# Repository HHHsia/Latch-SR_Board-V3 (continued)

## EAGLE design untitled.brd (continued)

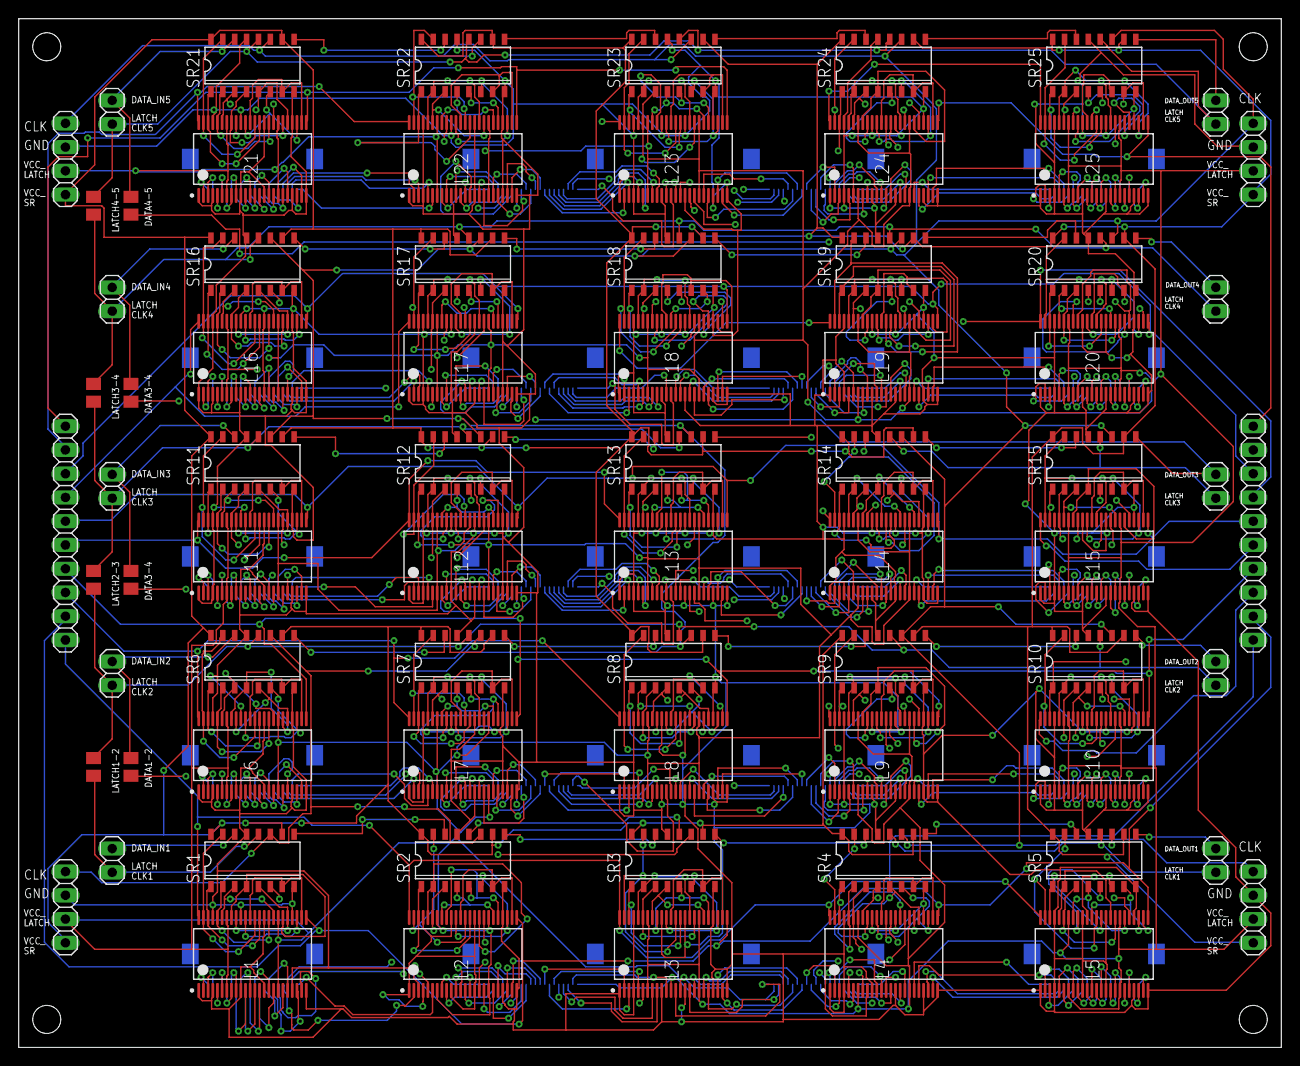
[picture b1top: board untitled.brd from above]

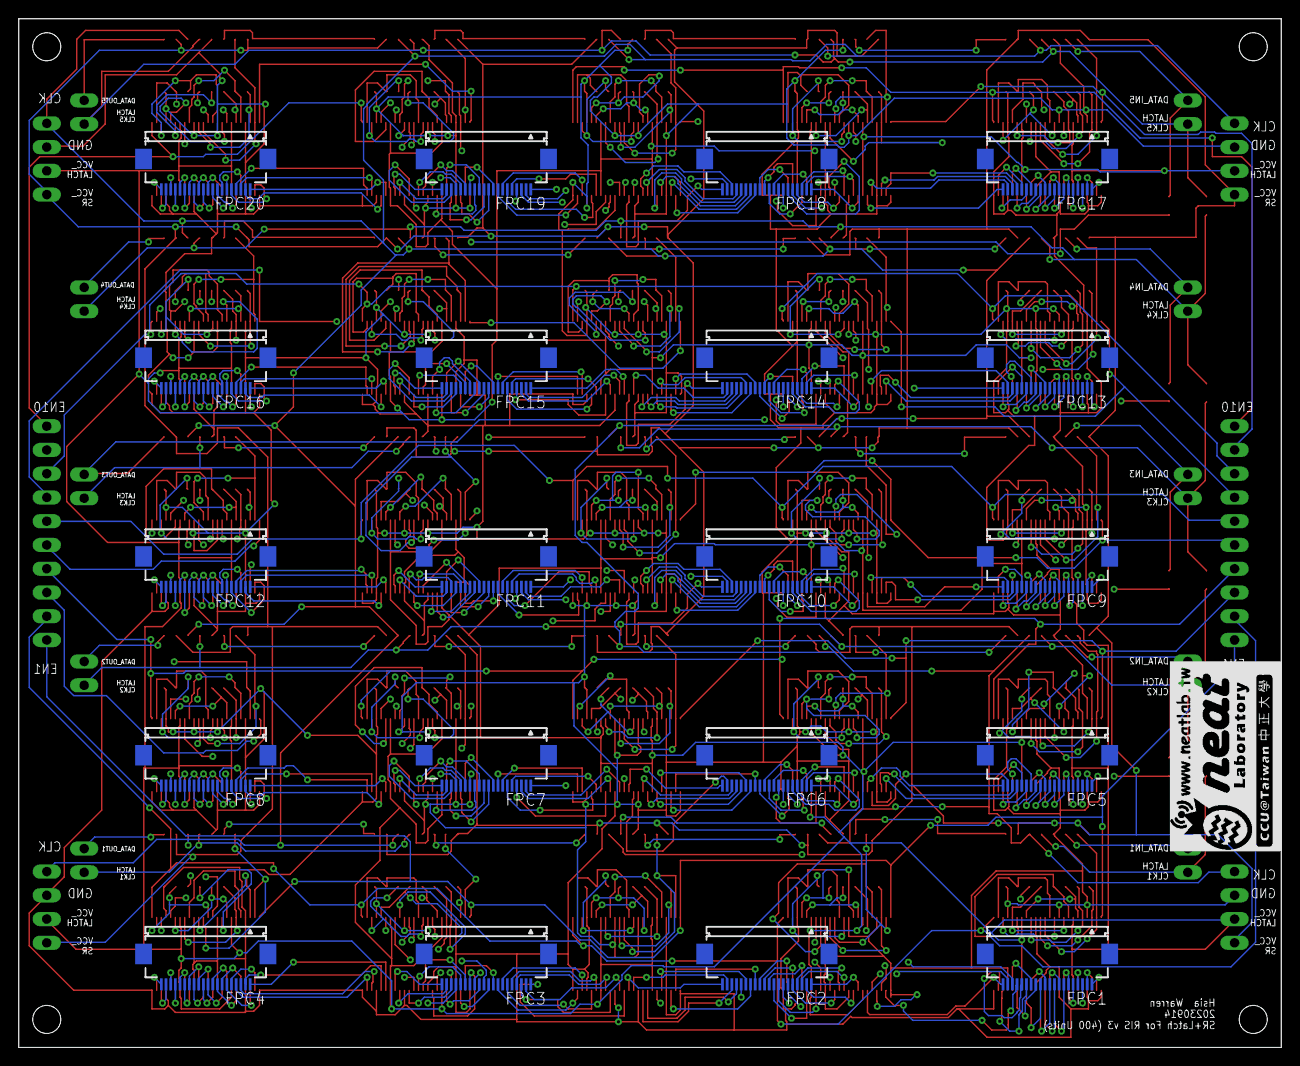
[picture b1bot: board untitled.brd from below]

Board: 4 copper layers, 135.0 x 110.0 mm, 95 parts (21 on the bottom side), 649 nets.

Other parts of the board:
U$1: LOGO_SCALE_2.0

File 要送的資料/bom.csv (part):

"Part";"Value";"Device";"Package";"Description";"3_STATE_OUTPUT";"AVAILABILITY";"BITS";"CIIVA_IDS";"CODE__JEDEC";"DATASHEET_VERSION";"DESCRIPTION";"FOOTPRINT_VARIANT_NAME_0";"FOOTPRINT_VARIANT_NAME_1";"FOOTPRINT_VARIANT_NAME_2";"F__NOM_VOLTAGEMAXMHZ";"ICC__NOM_VOLTAGEMAXMA";"IMPORTED";"IMPORTED_FROM";"IMPORT_TS";"INPUT_TYPE";"LOGIC";"MF";"MP";"MPN";"OC_FARNELL";"OC_NEWARK";"OPERATING_TEMPERATURE_RANGEC";"OUTPUT_DRIVE_IOLIOHMAXMA";"OUTPUT_LOGIC";"OUTPUT_TYPE";"PACKAGE";"POPULARITY";"PREFIX";"PRICE";"RATING";"RELEASE_DATE";"SCHMITT_TRIGGER";"SPICEPREFIX";"STATIC_CURRENT";"TECHNOLOGY_FAMILY";"TPD__NOM_VOLTAGEMAXNS";"VAULT_GUID";"VAULT_REVISION";"VCC_MAX_V";"VCC_MIN_V";"VOLTAGE_NOM_V";
"CONNECTION_BETWEEN_SR5-6";"0R";"R-US_M0805";"M0805";"RESISTOR, American symbol";"";"";"";"";"";"";"";"";"";"";"";"";"";"";"";"";"";"";"";"";"";"";"";"";"";"";"";"45";"";"";"";"";"";"R";"";"";"";"";"";"";"";"";
"CONNECTION_BETWEEN_SR10-11";"0R";"R-US_M0805";"M0805";"RESISTOR, American symbol";"";"";"";"";"";"";"";"";"";"";"";"";"";"";"";"";"";"";"";"";"";"";"";"";"";"";"";"45";"";"";"";"";"";"R";"";"";"";"";"";"";"";"";
"CONNECTION_BETWEEN_SR15-16";"0R";"R-US_M0805";"M0805";"RESISTOR, American symbol";"";"";"";"";"";"";"";"";"";"";"";"";"";"";"";"";"";"";"";"";"";"";"";"";"";"";"";"45";"";"";"";"";"";"R";"";"";"";"";"";"";"";"";
"CONNECTION_BETWEEN_SR20-21";"0R";"R-US_M0805";"M0805";"RESISTOR, American symbol";"";"";"";"";"";"";"";"";"";"";"";"";"";"";"";"";"";"";"";"";"";"";"";"";"";"";"";"45";"";"";"";"";"";"R";"";"";"";"";"";"";"";"";
"EN_JP1";"";"PINHD-1X10";"1X10";"PIN HEADER";"";"";"";"";"";"";"";"";"";"";"";"";"";"";"";"";"";"";"";"";"";"";"";"";"";"";"";"35";"";"";"";"";"";"";"";"";"";"";"";"";"";"";
"EN_JP2";"";"PINHD-1X10";"1X10";"PIN HEADER";"";"";"";"";"";"";"";"";"";"";"";"";"";"";"";"";"";"";"";"";"";"";"";"";"";"";"";"35";"";"";"";"";"";"";"";"";"";"";"";"";"";"";
"FPC1";"FH12-20S-0.5SH";"FH12-20S-0.5SH";"FH12-20S-0.5SH";"0.5mm Pitch Connectors For FPC/FFC";"";"";"";"";"";"";"";"";"";"";"";"";"";"";"";"";"";"";"";"FH12-20S-0.5SH(55)";"1324549";"34M6166";"";"";"";"";"";"0";"";"";"";"";"";"";"";"";"";"";"";"";"";"";
"FPC2";"FH12-20S-0.5SH";"FH12-20S-0.5SH";"FH12-20S-0.5SH";"0.5mm Pitch Connectors For FPC/FFC";"";"";"";"";"";"";"";"";"";"";"";"";"";"";"";"";"";"";"";"FH12-20S-0.5SH(55)";"1324549";"34M6166";"";"";"";"";"";"0";"";"";"";"";"";"";"";"";"";"";"";"";"";"";
"FPC3";"FH12-20S-0.5SH";"FH12-20S-0.5SH";"FH12-20S-0.5SH";"0.5mm Pitch Connectors For FPC/FFC";"";"";"";"";"";"";"";"";"";"";"";"";"";"";"";"";"";"";"";"FH12-20S-0.5SH(55)";"1324549";"34M6166";"";"";"";"";"";"0";"";"";"";"";"";"";"";"";"";"";"";"";"";"";
"FPC4";"FH12-20S-0.5SH";"FH12-20S-0.5SH";"FH12-20S-0.5SH";"0.5mm Pitch Connectors For FPC/FFC";"";"";"";"";"";"";"";"";"";"";"";"";"";"";"";"";"";"";"";"FH12-20S-0.5SH(55)";"1324549";"34M6166";"";"";"";"";"";"0";"";"";"";"";"";"";"";"";"";"";"";"";"";"";
"FPC5";"FH12-20S-0.5SH";"FH12-20S-0.5SH";"FH12-20S-0.5SH";"0.5mm Pitch Connectors For FPC/FFC";"";"";"";"";"";"";"";"";"";"";"";"";"";"";"";"";"";"";"";"FH12-20S-0.5SH(55)";"1324549";"34M6166";"";"";"";"";"";"0";"";"";"";"";"";"";"";"";"";"";"";"";"";"";
"FPC6";"FH12-20S-0.5SH";"FH12-20S-0.5SH";"FH12-20S-0.5SH";"0.5mm Pitch Connectors For FPC/FFC";"";"";"";"";"";"";"";"";"";"";"";"";"";"";"";"";"";"";"";"FH12-20S-0.5SH(55)";"1324549";"34M6166";"";"";"";"";"";"0";"";"";"";"";"";"";"";"";"";"";"";"";"";"";
"FPC7";"FH12-20S-0.5SH";"FH12-20S-0.5SH";"FH12-20S-0.5SH";"0.5mm Pitch Connectors For FPC/FFC";"";"";"";"";"";"";"";"";"";"";"";"";"";"";"";"";"";"";"";"FH12-20S-0.5SH(55)";"1324549";"34M6166";"";"";"";"";"";"0";"";"";"";"";"";"";"";"";"";"";"";"";"";"";
"FPC8";"FH12-20S-0.5SH";"FH12-20S-0.5SH";"FH12-20S-0.5SH";"0.5mm Pitch Connectors For FPC/FFC";"";"";"";"";"";"";"";"";"";"";"";"";"";"";"";"";"";"";"";"FH12-20S-0.5SH(55)";"1324549";"34M6166";"";"";"";"";"";"0";"";"";"";"";"";"";"";"";"";"";"";"";"";"";
"FPC9";"FH12-20S-0.5SH";"FH12-20S-0.5SH";"FH12-20S-0.5SH";"0.5mm Pitch Connectors For FPC/FFC";"";"";"";"";"";"";"";"";"";"";"";"";"";"";"";"";"";"";"";"FH12-20S-0.5SH(55)";"1324549";"34M6166";"";"";"";"";"";"0";"";"";"";"";"";"";"";"";"";"";"";"";"";"";
"FPC10";"FH12-20S-0.5SH";"FH12-20S-0.5SH";"FH12-20S-0.5SH";"0.5mm Pitch Connectors For FPC/FFC";"";"";"";"";"";"";"";"";"";"";"";"";"";"";"";"";"";"";"";"FH12-20S-0.5SH(55)";"1324549";"34M6166";"";"";"";"";"";"0";"";"";"";"";"";"";"";"";"";"";"";"";"";"";
"FPC11";"FH12-20S-0.5SH";"FH12-20S-0.5SH";"FH12-20S-0.5SH";"0.5mm Pitch Connectors For FPC/FFC";"";"";"";"";"";"";"";"";"";"";"";"";"";"";"";"";"";"";"";"FH12-20S-0.5SH(55)";"1324549";"34M6166";"";"";"";"";"";"0";"";"";"";"";"";"";"";"";"";"";"";"";"";"";
"FPC12";"FH12-20S-0.5SH";"FH12-20S-0.5SH";"FH12-20S-0.5SH";"0.5mm Pitch Connectors For FPC/FFC";"";"";"";"";"";"";"";"";"";"";"";"";"";"";"";"";"";"";"";"FH12-20S-0.5SH(55)";"1324549";"34M6166";"";"";"";"";"";"0";"";"";"";"";"";"";"";"";"";"";"";"";"";"";
"FPC13";"FH12-20S-0.5SH";"FH12-20S-0.5SH";"FH12-20S-0.5SH";"0.5mm Pitch Connectors For FPC/FFC";"";"";"";"";"";"";"";"";"";"";"";"";"";"";"";"";"";"";"";"FH12-20S-0.5SH(55)";"1324549";"34M6166";"";"";"";"";"";"0";"";"";"";"";"";"";"";"";"";"";"";"";"";"";
"FPC14";"FH12-20S-0.5SH";"FH12-20S-0.5SH";"FH12-20S-0.5SH";"0.5mm Pitch Connectors For FPC/FFC";"";"";"";"";"";"";"";"";"";"";"";"";"";"";"";"";"";"";"";"FH12-20S-0.5SH(55)";"1324549";"34M6166";"";"";"";"";"";"0";"";"";"";"";"";"";"";"";"";"";"";"";"";"";
"FPC15";"FH12-20S-0.5SH";"FH12-20S-0.5SH";"FH12-20S-0.5SH";"0.5mm Pitch Connectors For FPC/FFC";"";"";"";"";"";"";"";"";"";"";"";"";"";"";"";"";"";"";"";"FH12-20S-0.5SH(55)";"1324549";"34M6166";"";"";"";"";"";"0";"";"";"";"";"";"";"";"";"";"";"";"";"";"";
"FPC16";"FH12-20S-0.5SH";"FH12-20S-0.5SH";"FH12-20S-0.5SH";"0.5mm Pitch Connectors For FPC/FFC";"";"";"";"";"";"";"";"";"";"";"";"";"";"";"";"";"";"";"";"FH12-20S-0.5SH(55)";"1324549";"34M6166";"";"";"";"";"";"0";"";"";"";"";"";"";"";"";"";"";"";"";"";"";
"FPC17";"FH12-20S-0.5SH";"FH12-20S-0.5SH";"FH12-20S-0.5SH";"0.5mm Pitch Connectors For FPC/FFC";"";"";"";"";"";"";"";"";"";"";"";"";"";"";"";"";"";"";"";"FH12-20S-0.5SH(55)";"1324549";"34M6166";"";"";"";"";"";"0";"";"";"";"";"";"";"";"";"";"";"";"";"";"";
"FPC18";"FH12-20S-0.5SH";"FH12-20S-0.5SH";"FH12-20S-0.5SH";"0.5mm Pitch Connectors For FPC/FFC";"";"";"";"";"";"";"";"";"";"";"";"";"";"";"";"";"";"";"";"FH12-20S-0.5SH(55)";"1324549";"34M6166";"";"";"";"";"";"0";"";"";"";"";"";"";"";"";"";"";"";"";"";"";
"FPC19";"FH12-20S-0.5SH";"FH12-20S-0.5SH";"FH12-20S-0.5SH";"0.5mm Pitch Connectors For FPC/FFC";"";"";"";"";"";"";"";"";"";"";"";"";"";"";"";"";"";"";"";"FH12-20S-0.5SH(55)";"1324549";"34M6166";"";"";"";"";"";"0";"";"";"";"";"";"";"";"";"";"";"";"";"";"";
"FPC20";"FH12-20S-0.5SH";"FH12-20S-0.5SH";"FH12-20S-0.5SH";"0.5mm Pitch Connectors For FPC/FFC";"";"";"";"";"";"";"";"";"";"";"";"";"";"";"";"";"";"";"";"FH12-20S-0.5SH(55)";"1324549";"34M6166";"";"";"";"";"";"0";"";"";"";"";"";"";"";"";"";"";"";"";"";"";
"IN_JP1";"";"PINHD-1X2";"1X02";"PIN HEADER";"";"";"";"";"";"";"";"";"";"";"";"";"";"";"";"";"";"";"";"";"";"";"";"";"";"";"";"98";"";"";"";"";"";"";"";"";"";"";"";"";"";"";
"IN_JP2";"";"PINHD-1X2";"1X02";"PIN HEADER";"";"";"";"";"";"";"";"";"";"";"";"";"";"";"";"";"";"";"";"";"";"";"";"";"";"";"";"98";"";"";"";"";"";"";"";"";"";"";"";"";"";"";
"IN_JP3";"";"PINHD-1X2";"1X02";"PIN HEADER";"";"";"";"";"";"";"";"";"";"";"";"";"";"";"";"";"";"";"";"";"";"";"";"";"";"";"";"98";"";"";"";"";"";"";"";"";"";"";"";"";"";"";
"IN_JP4";"";"PINHD-1X2";"1X02";"PIN HEADER";"";"";"";"";"";"";"";"";"";"";"";"";"";"";"";"";"";"";"";"";"";"";"";"";"";"";"";"98";"";"";"";"";"";"";"";"";"";"";"";"";"";"";
"IN_JP5";"";"PINHD-1X2";"1X02";"PIN HEADER";"";"";"";"";"";"";"";"";"";"";"";"";"";"";"";"";"";"";"";"";"";"";"";"";"";"";"";"98";"";"";"";"";"";"";"";"";"";"";"";"";"";"";
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
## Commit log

2024-07-05 0705
2024-07-05 刪除不必要檔案
2024-07-10 0710
